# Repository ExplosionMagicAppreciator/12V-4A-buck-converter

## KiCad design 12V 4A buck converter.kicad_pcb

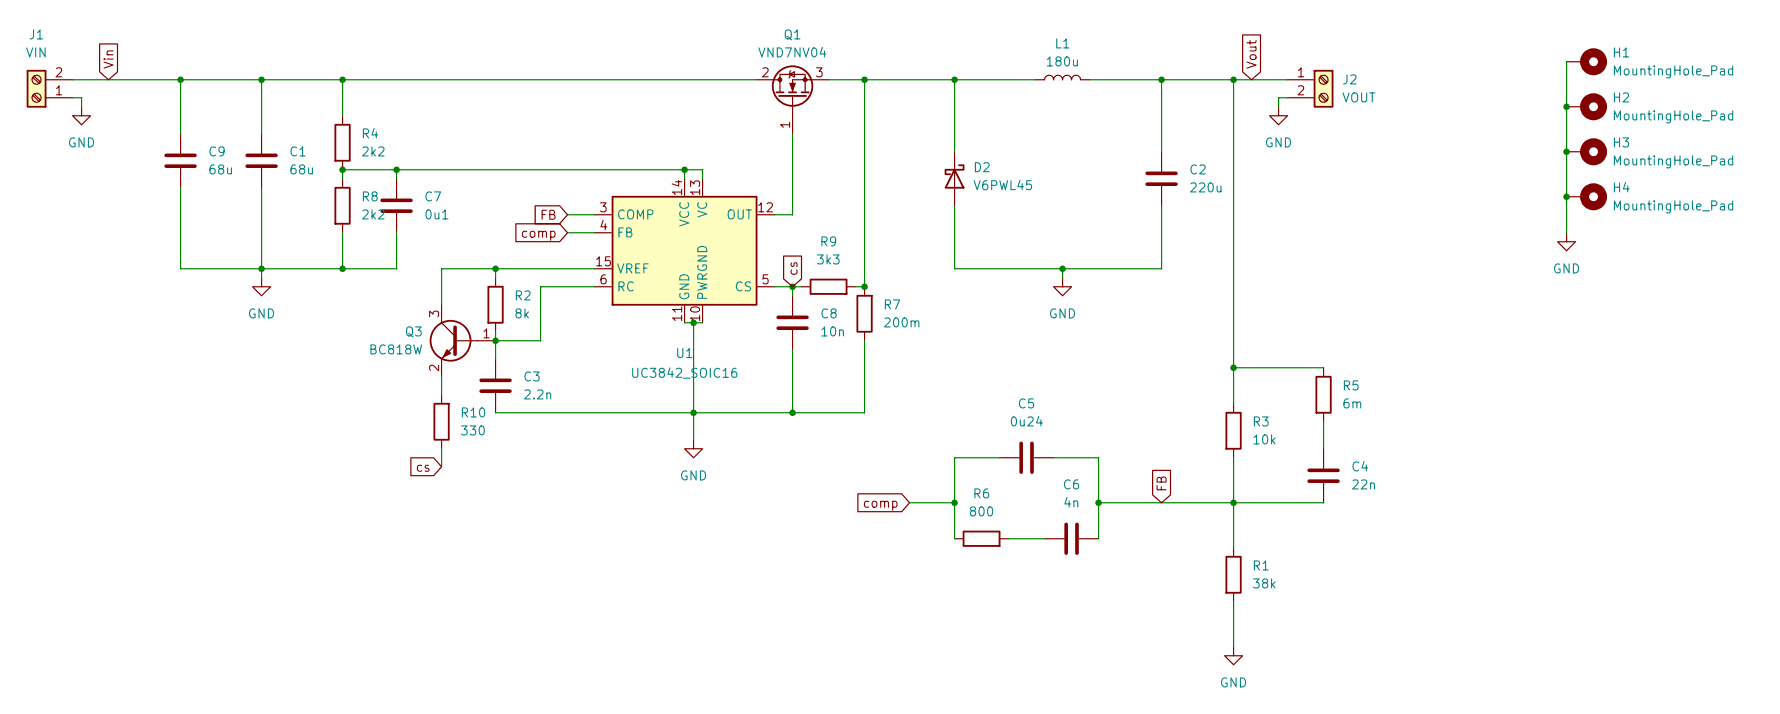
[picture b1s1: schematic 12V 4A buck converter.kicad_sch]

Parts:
C1, C9: 68u; C_Elec_8x10.2
C2: 220u; C_Elec_6.3x7.7
C3: 2.2n; C_0402_1005Metric
C4: 22n; C_0805_2012Metric
C5: 0u24; C_1206_3216Metric
C6: 4n; C_0603_1608Metric
C7: 0u1; C_0805_2012Metric
C8: 10n; C_0603_1608Metric
D2: V6PWL45; TO-252-2_TabPin1
H1, H2, H3, H4: MountingHole_Pad; MountingHole_3.2mm_M3_DIN965_Pad
J1: VIN; TerminalBlock_Phoenix_MPT-0,5-2-2.54_1x02_P2.54mm_Horizontal
J2: VOUT; TerminalBlock_Phoenix_MPT-0,5-2-2.54_1x02_P2.54mm_Horizontal
L1: 180u; L_Toroid_Vertical_L24.6mm_W15.5mm_P11.44mm_Pulse_KM-4
Q1: VND7NV04; TO-252-2
Q3: BC818W; SOT-323_SC-70
R1: 38k; R_1210_3225Metric
R2: 8k; R_0603_1608Metric
R3: 10k; R_1210_3225Metric
R4, R8: 2k2; R_1210_3225Metric
R5: 6m; R_1210_3225Metric
R6: 800; R_0603_1608Metric
R7: 200m; R_2816_7142Metric
R9: 3k3; R_0603_1608Metric
R10: 330; R_0603_1608Metric
U1: UC3842_SOIC16; SOIC-16W_7.5x10.3mm_P1.27mm

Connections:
FB: C4.2, C5.1, C6.2, R1.1, R3.2, U1.3 (COMP)
GND: C1.1, C2.1, C3.2, C7.2, C8.2, C9.1, D2.2 (A), H1.1, H2.1, H3.1, H4.1, J1.1, J2.2, R1.2, R7.1, R8.2, U1.10 (PWRGND), U1.11 (GND)
unnamed: C4.1, R5.2
unnamed: C6.1, R6.2
unnamed: D2.1 (K), L1.1, Q1.3 (S), R7.2, R9.2
unnamed: Q1.1 (G), U1.12 (OUT)
unnamed: C3.1, Q3.1 (B), R2.2, U1.6 (RC)
unnamed: Q3.3 (C), R2.1, U1.15 (VREF)
unnamed: Q3.2 (E), R10.2
unnamed: C7.1, R4.2, R8.1, U1.13 (VC), U1.14 (VCC)
Vin: C1.2, C9.2, J1.2, Q1.2 (D), R4.1
Vout: C2.2, J2.1, L1.2, R3.1, R5.1
comp: C5.2, R6.1, U1.4 (FB)
cs: C8.1, R9.1, R10.1, U1.5 (CS)

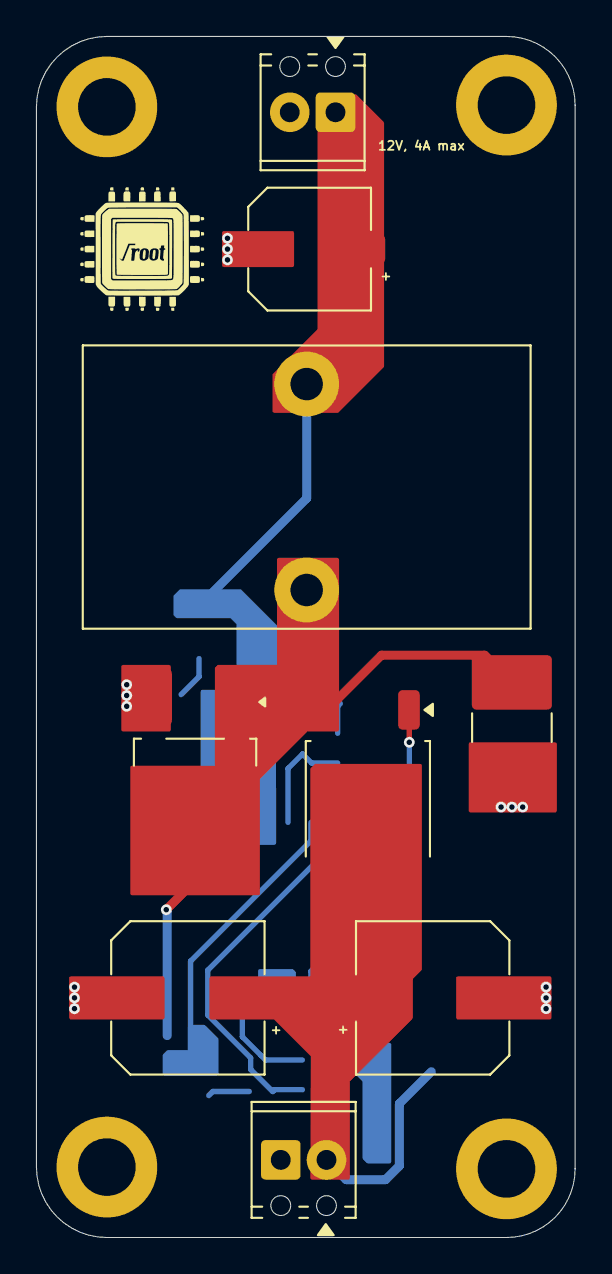
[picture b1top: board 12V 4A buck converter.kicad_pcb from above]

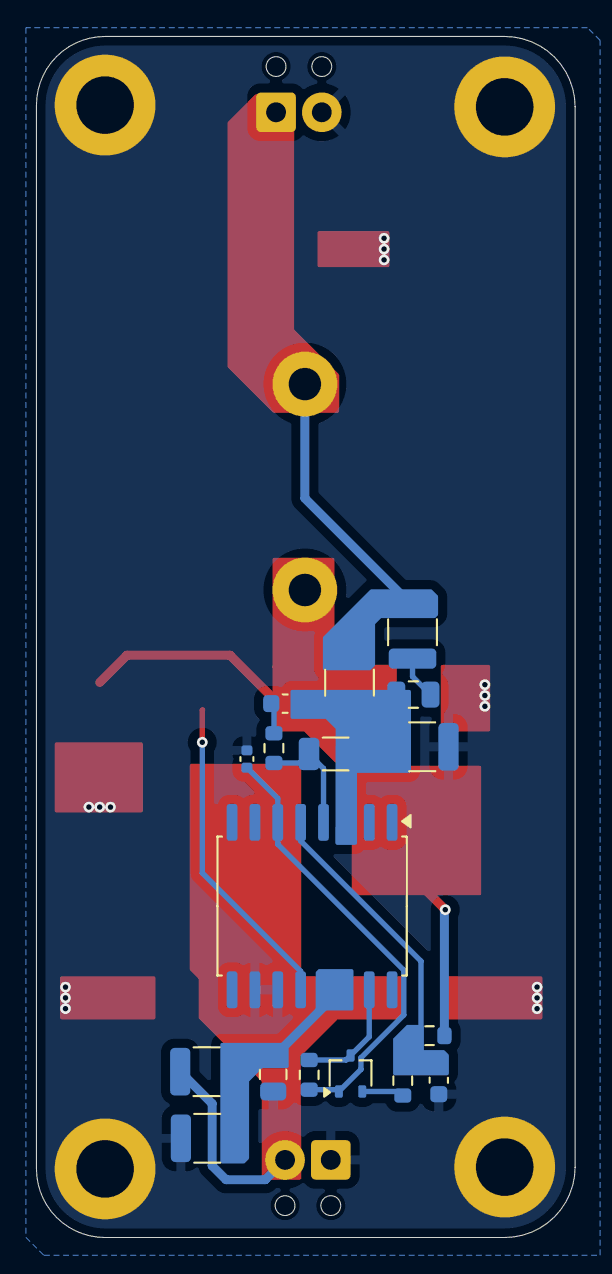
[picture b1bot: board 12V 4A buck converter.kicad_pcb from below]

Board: 2 copper layers, 29.9 x 66.7 mm, 30 parts (17 on the bottom side), 14 nets.

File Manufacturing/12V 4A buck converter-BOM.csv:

"Reference","Qty","Value","DNP","Exclude from BOM","Exclude from Board","Footprint","Datasheet"
"C1,C9","2","68u","","","","Capacitor_SMD:C_Elec_8x10.2","~"
"C2","1","220u","","","","Capacitor_SMD:C_Elec_6.3x7.7","~"
"C3","1","2.2n","","","","Capacitor_SMD:C_0402_1005Metric","~"
"C4","1","22n","","","","Capacitor_SMD:C_0805_2012Metric","~"
"C5","1","0u24","","","","Capacitor_SMD:C_1206_3216Metric","~"
"C6","1","4n","","","","Capacitor_SMD:C_0603_1608Metric","~"
"C7","1","0u1","","","","Capacitor_SMD:C_0805_2012Metric","~"
"C8","1","10n","","","","Capacitor_SMD:C_0603_1608Metric","~"
"D2","1","V6PWL45","","","","Package_TO_SOT_SMD:TO-252-2_TabPin1","https://www.vishay.com/docs/98173/v6pwl45.pdf"
"J1","1","VIN","","","","TerminalBlock_Phoenix:TerminalBlock_Phoenix_MPT-0,5-2-2.54_1x02_P2.54mm_Horizontal","~"
"J2","1","VOUT","","","","TerminalBlock_Phoenix:TerminalBlock_Phoenix_MPT-0,5-2-2.54_1x02_P2.54mm_Horizontal","~"
"L1","1","180u","","","","Inductor_THT:L_Toroid_Vertical_L24.6mm_W15.5mm_P11.44mm_Pulse_KM-4","~"
"Q1","1","VND7NV04","","","","Package_TO_SOT_SMD:TO-252-2","https://www.st.com/resource/en/datasheet/vnd7nv04.pdf"
"Q3","1","BC818W","","","","Package_TO_SOT_SMD:SOT-323_SC-70","https://www.onsemi.com/pub/Collateral/BC818-D.pdf"
"R1","1","38k","","","","Resistor_SMD:R_1210_3225Metric","~"
"R2","1","8k","","","","Resistor_SMD:R_0603_1608Metric","~"
"R3","1","10k","","","","Resistor_SMD:R_1210_3225Metric","~"
"R4,R8","2","2k2","","","","Resistor_SMD:R_1210_3225Metric","~"
"R5","1","6m","","","","Resistor_SMD:R_1210_3225Metric","~"
"R6","1","800","","","","Resistor_SMD:R_0603_1608Metric","~"
"R7","1","200m","","","","Resistor_SMD:R_2816_7142Metric","~"
"R9","1","3k3","","","","Resistor_SMD:R_0603_1608Metric","~"
"R10","1","330","","","","Resistor_SMD:R_0603_1608Metric","~"
"U1","1","UC3842_SOIC16","","","","Package_SO:SOIC-16W_7.5x10.3mm_P1.27mm","http://www.ti.com/lit/ds/symlink/uc2843a.pdf"
